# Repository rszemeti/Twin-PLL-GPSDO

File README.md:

# Twin PLL GPSDO

A dual-output GPS-disciplined reference project for Raspberry Pi Pico 2 (RP2350), with:
- Firmware for GPSDO control + PLL programming
- A desktop configuration tool (Windows-friendly)
- A PCB with 2 ADF4351's, GPS module and all the interface bits

## Who this is for
If you need a stable, GPS locked signal source for injection locking 1 or 2 crystal oscillators, or at a push a directly synthesised carrier up to 4.4 GHz.  

It has the advantage over some other units in that the two outputs are truly independently programmable. If you have a microwave transverter for example that needs injection locking and then a 144 to 28MHz converter, you often find that many units only allow the second output to be a fraction of the primary output, which may not produce thw 116 MHz you need. This unit has 2 synthesisers each of which can be programmed as desired.

## Features
- **Output 1 / Output 2 PLL**  Truly indpendent of each other
- **10MHz Auxilliary Output**  For driving other items, eg main radio.
- **Persistent settings** (ADF register writes are auto-committed to EEPROM)
- **Live status LEDs** (GPS fix/lock, satellites, DOP, alarm, lock states)
- **Windows configuration tool** with Main/Details/Tuning/About tabs

## RF output notes
- **Two outputs are fully independent**: each PLL output has its own register set and can be tuned separately.
- **Frequency range**: any frequency within the ADF4351 synthesizer output range is supported in software (approximately **34.375 MHz to 4.4 GHz**).
	- Practical usable range depends on your board layout, output network, filtering, and measurement method.
- **Resolution / step size**:
	- In **Integer-N**, tuning is quantized by $f_{PFD}/\text{OUTDIV}$.
	- With default settings (10 MHz ref, R=5, so $f_{PFD}=2$ MHz), Integer-N step is $2\text{ MHz}/\text{OUTDIV}$ (for example, 62.5 kHz at OUTDIV=32).
	- In **Fractional-N**, finer step sizes are possible (GUI default channel spacing is 1 Hz), but with fractional spurs/tradeoffs.
- **Phase-noise tradeoff**:
	- **Integer-N** is generally preferred for best close-in noise / cleaner spectrum when an exact frequency is possible.
	- **Fractional-N** gives finer frequency placement when exact Integer-N is not available, but may increase spur content.
- **Intended use guidance**:
	- Phase noise is typically **good enough for injection-locking crystal multipliers**.
	- It may **not** be good enough for all **direct multiplication** chains, depending on your multiplier stages and phase-noise budget.

## Repository layout
- `firmware/` – PlatformIO project for Pico 2
- `monitor/` – Python GUI configuration tool app
- `.github/workflows/` – release build automation
- `REFERENCE_LOCKING_README.md` – technical notes on GPS reference locking, PIO timing, interrupts, and timing/error budget

## Quick start (recommended)
### 1) Download a Release
From GitHub Releases, download:
- `Twin-PLL-GPSDO-<tag>.uf2` (firmware)
- `TwinPLLGPSDOMonitor-<tag>.exe` (Windows configuration tool)

### 2) Flash firmware (`.uf2`)
1. Put Pico 2 into BOOTSEL mode.
2. Copy the `.uf2` file to the mounted RP drive.
3. Board reboots automatically.

### 3) Run the configuration tool (`.exe`)
1. Start `TwinPLLGPSDOMonitor-<tag>.exe`.
2. Select COM port and click **Connect**.
3. Use **Set O/P 1** / **Set O/P 2** to configure outputs.

---

## Build from source
## Firmware
Prerequisites:
- Python 3.11+
- PlatformIO

Commands:
```bash
cd firmware
python -m platformio run
```
Upload (example COM port):
```bash
python -m platformio run -t upload --upload-port COM7
```

## Configuration tool (Python)
Prerequisites:
- Python 3.11+

Commands:
```bash
cd monitor
python -m venv .venv
.venv\Scripts\activate
pip install -r requirements.txt
python gpsdo_monitor.py
```

## Configuration tool usage notes
- **Main tab**: front-panel style status + output frequencies + output set buttons
- **Details tab**: logs, decoded registers, DAC/state details
- **About tab**: project links and author links

The configuration tool supports JSON command send for advanced/manual control.

## Persistence behavior
When a PLL/program command is applied:
- Registers are staged
- EEPROM auto-commit is performed in firmware
- On success, firmware emits a success event and the configuration tool shows **Device Updated**

## Releases and updates
On published release, GitHub Actions builds and attaches:
- Firmware UF2
- Configuration tool one-file EXE

So most users can update without local toolchains.

## Troubleshooting
- **Configuration tool cannot connect**: verify correct COM port and close other serial tools.
- **No lock / unstable GPS**: verify antenna visibility and allow warm-up time.
- **Upload issues on Windows**: retry BOOTSEL entry and ensure USB cable supports data.

## Author / links
- Robin Szemeti, G1YFG
- QRZ: https://www.qrz.com/db/G1YFG
- Blog: https://g1yfg.blogspot.com/
- Project repo: https://github.com/rszemeti/Twin-PLL-GPSDO

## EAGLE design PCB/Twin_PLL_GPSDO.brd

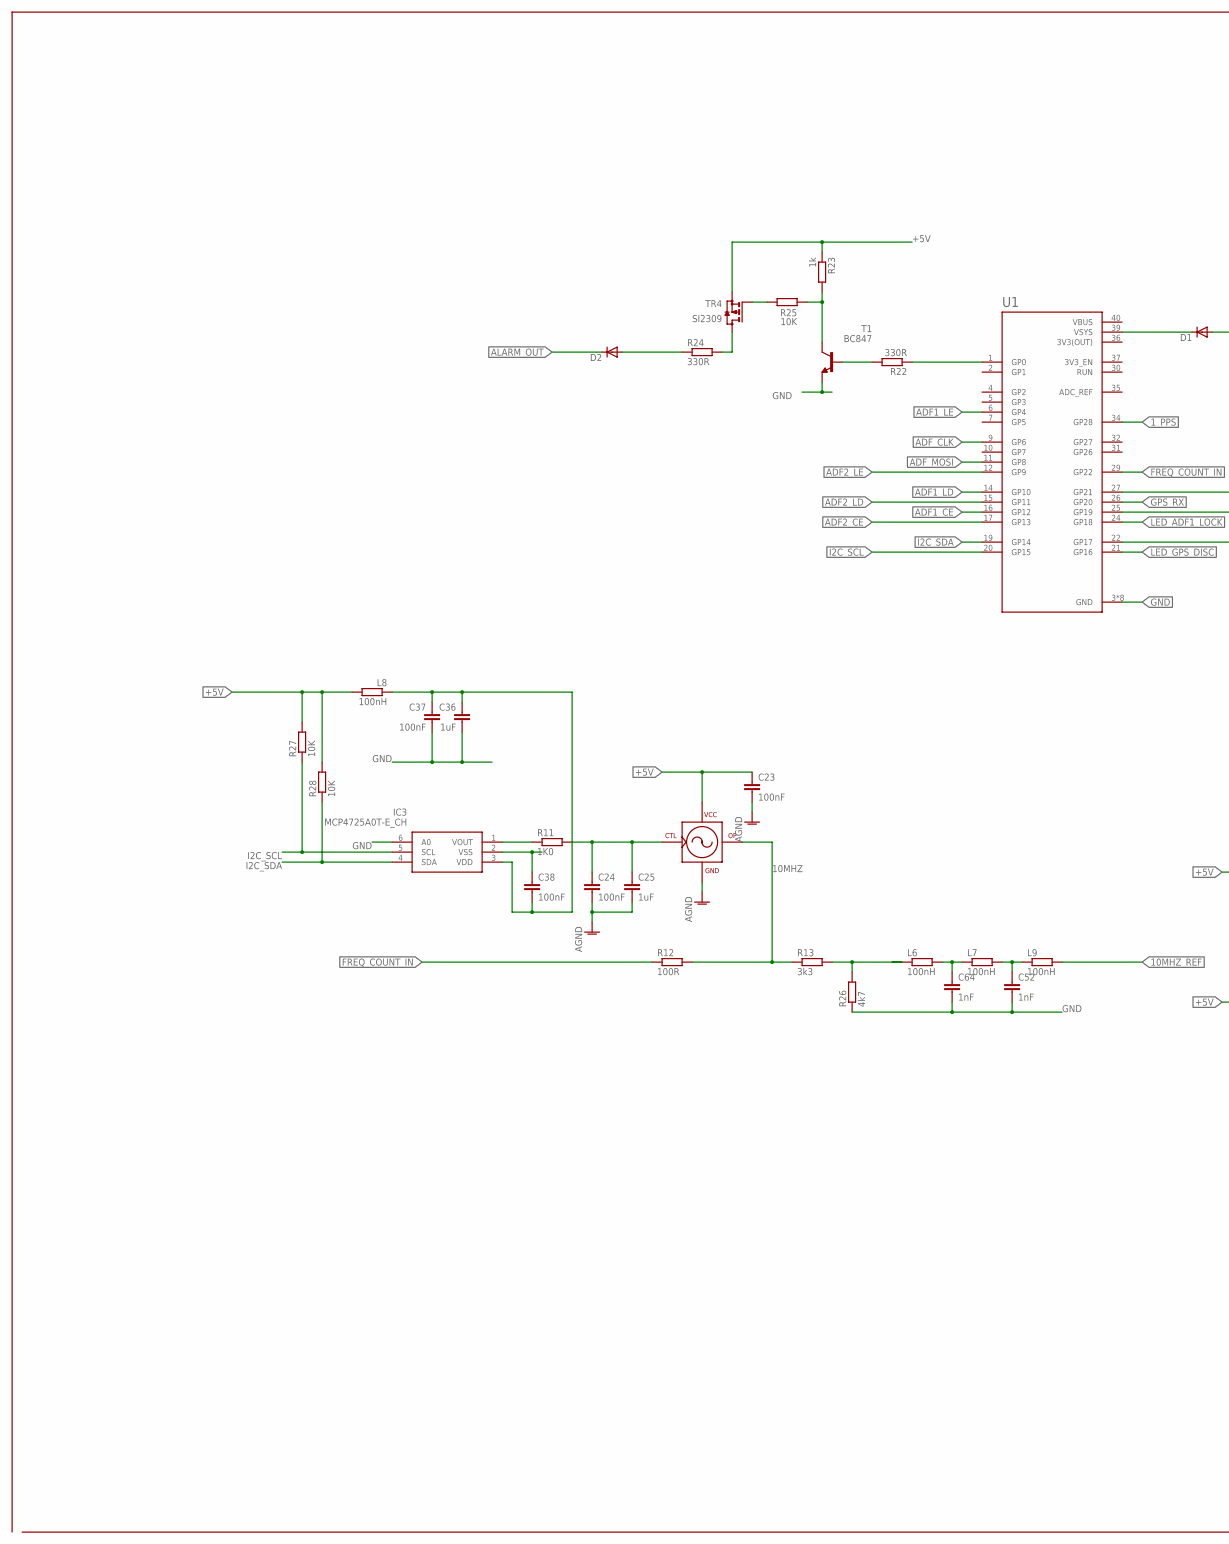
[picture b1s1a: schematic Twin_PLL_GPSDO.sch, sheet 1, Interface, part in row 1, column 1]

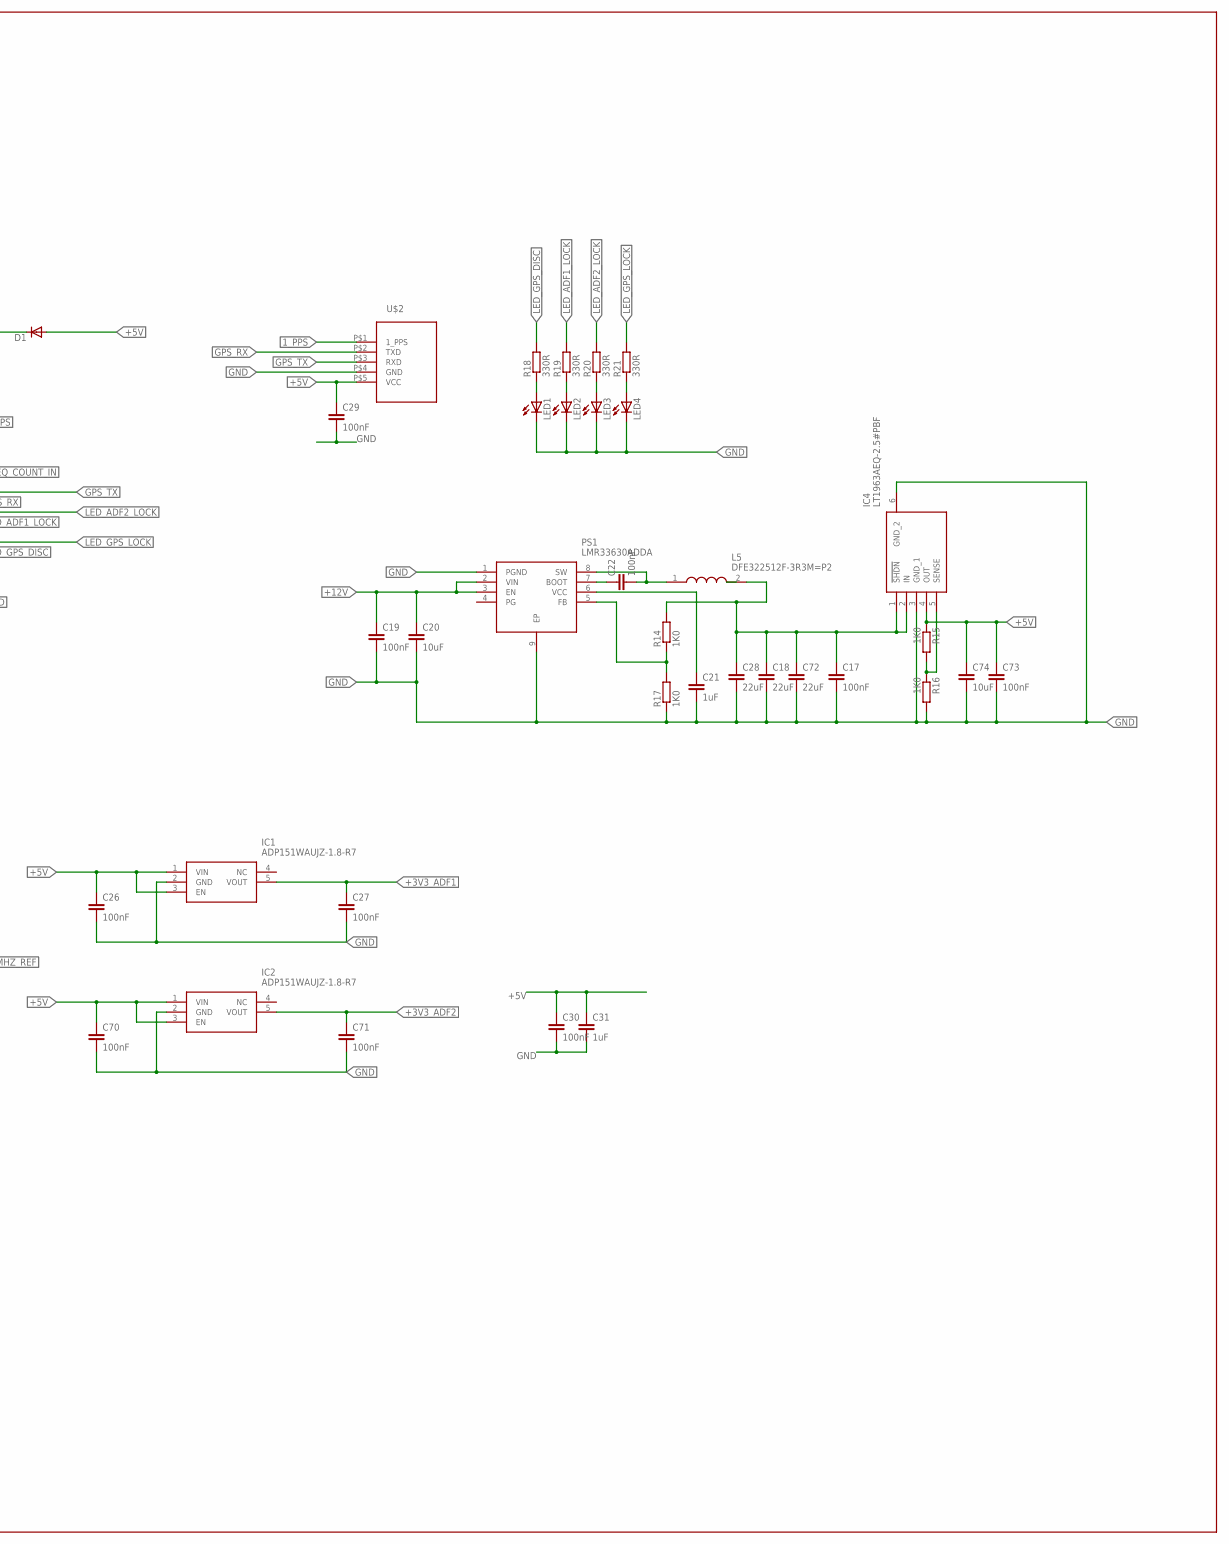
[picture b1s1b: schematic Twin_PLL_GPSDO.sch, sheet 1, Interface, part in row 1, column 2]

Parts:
C17, C19, C22, C26, C27, C29, C70, C71, C73: 100nF; C0805
C18, C28, C72: 22uF; C1210
C20, C74: 10uF; C0805
C21: 1uF; C0805
C23, C24, C30, C37, C38: 100nF; C0603
C25, C31, C36: 1uF; C0603
C52, C64: 1nF; C0603
D1, D2: DIODE-SOD123; SOD123
IC1, IC2: ADP151WAUJZ-1.8-R7; SOT95P280X100-5N
IC3: MCP4725A0T-E_CH; SOT95P270X145-6N
IC4: LT1963AEQ-2.5#PBF; LT1963AEQ25PBF
L5: DFE322512F-3R3M=P2; 1277ASH100MP2; FARNELL_OC 2871467
L6, L7, L8, L9: 100nH; R0603
LED1, LED2, LED3, LED4: LEDCHIPLED_0603; CHIPLED_0603
OSC1: CTI_OSC
PS1: LMR33630ADDA; SOIC127P600X170-9N
R11, R14, R15, R16, R17: 1K0; R0805
R12: 100R; R0805
R13: 3k3; R0603
R18, R19, R20, R21, R22: 330R; R0603
R23: 1k; R0603
R24: 330R; R0805
R25: 10K; R0805
R26: 4k7; R0603
R27, R28: 10K; R0603
T1: BC847; SOT23
TR4: SI2309; SOT23
U1: RASPBERRY_PICO-NO_DEBUGTH; PICO-PKG-TH-STD
U$2: GPS

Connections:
1_PPS: U1.34 (GP28), U$2.P$1 (1_PPS)
3V3(OUT): U1.36 (3V3(OUT))
10MHZ: OSC1.OUT (OP), R12.2, R13.1
10MHZ_REF: L9.2; also elsewhere on the board
+3V3_ADF1: C27.1, IC1.5 (VOUT); also elsewhere on the board
+3V3_ADF2: C71.1, IC2.5 (VOUT); also elsewhere on the board
+5V: C23.1, C26.1, C29.1, C30.1, C31.1, C70.1, C73.1, C74.1, D1.A, IC1.1 (VIN), IC1.3 (EN), IC2.1 (VIN), IC2.3 (EN), IC4.4 (OUT), L8.2, OSC1.VCC, R15.1, R23.1, R27.2, R28.2, TR4.2 (S), U$2.P$5 (VCC)
+12V: C19.1, C20.1, PS1.2 (VIN), PS1.3 (EN)
ADF1_CE: U1.16 (GP12); also elsewhere on the board
ADF1_LD: U1.14 (GP10); also elsewhere on the board
ADF1_LE: U1.6 (GP4); also elsewhere on the board
ADF2_CE: U1.17 (GP13); also elsewhere on the board
ADF2_LD: U1.15 (GP11); also elsewhere on the board
ADF2_LE: U1.12 (GP9); also elsewhere on the board
ADF_CLK: U1.9 (GP6); also elsewhere on the board
ADF_MOSI: U1.11 (GP8); also elsewhere on the board
ALARM_OUT: D2.C
ALARM_PIN: R22.1, U1.1 (GP0)
AVDD: C36.1, C37.1, C38.2, IC3.3 (VDD), L8.1
FREQ_COUNT_IN: R12.1, U1.29 (GP22)
GND: C17.2, C18.2, C19.2, C20.2, C21.2, C23.2, C24.2, C25.2, C26.2, C27.2, C28.2, C29.2, C30.2, C31.2, C36.2, C37.2, C38.1, C52.2, C64.2, C70.2, C71.2, C72.2, C73.2, C74.2, IC1.2 (GND), IC2.2 (GND), IC3.2 (VSS), IC3.6 (A0), IC4.3 (GND_1), IC4.6 (GND_2), LED1.C, LED2.C, LED3.C, LED4.C, OSC1.GND, PS1.1 (PGND), PS1.9 (EP), R16.2, R17.1, R26.1, T1.2 (E), U1.3 (GND), U1.8 (GND), U1.13 (GND), U1.18 (GND), U1.23 (GND), U1.28 (GND), U1.33 (GND), U1.38 (GND), U$2.P$4 (GND); also elsewhere on the board
GPS_RX: U1.26 (GP20), U$2.P$2 (TXD)
GPS_TX: U1.27 (GP21), U$2.P$3 (RXD)
I2C_SCL: IC3.5 (SCL), R27.1, U1.20 (GP15)
I2C_SDA: IC3.4 (SDA), R28.1, U1.19 (GP14)
LED_ADF1_LOCK: R19.2, U1.24 (GP18)
LED_ADF2_LOCK: R20.2, U1.25 (GP19)
LED_GPS_DISC: R18.2, U1.21 (GP16)
LED_GPS_LOCK: R21.2, U1.22 (GP17)
unnamed: IC3.1 (VOUT), R11.1
unnamed: R23.2, R25.2, T1.3 (C)
unnamed: L6.1, R13.2, R26.2
unnamed: LED1.A, R18.1
unnamed: R22.2, T1.1 (B)
unnamed: IC4.5 (SENSE), R15.2, R16.1
unnamed: PS1.5 (FB), R14.1, R17.2
unnamed: C24.1, C25.1, OSC1.REF (CTRL), R11.2
unnamed: C21.1, PS1.6 (VCC)
unnamed: C22.1, PS1.7 (BOOT)
unnamed: C22.2, L5.1, PS1.8 (SW)
unnamed: C17.1, C18.1, C28.1, C72.1, IC4.1 (!SHDN), IC4.2 (IN), L5.2, R14.2
unnamed: LED2.A, R19.1
unnamed: LED3.A, R20.1
unnamed: LED4.A, R21.1
unnamed: D1.C, U1.39 (VSYS)
unnamed: C64.1, L6.2, L7.1
unnamed: R25.1, TR4.1 (G)
unnamed: C52.1, L7.2, L9.1
unnamed: D2.A, R24.1
SWITCH: R24.2, TR4.3 (D)
VBUS: U1.40 (VBUS)

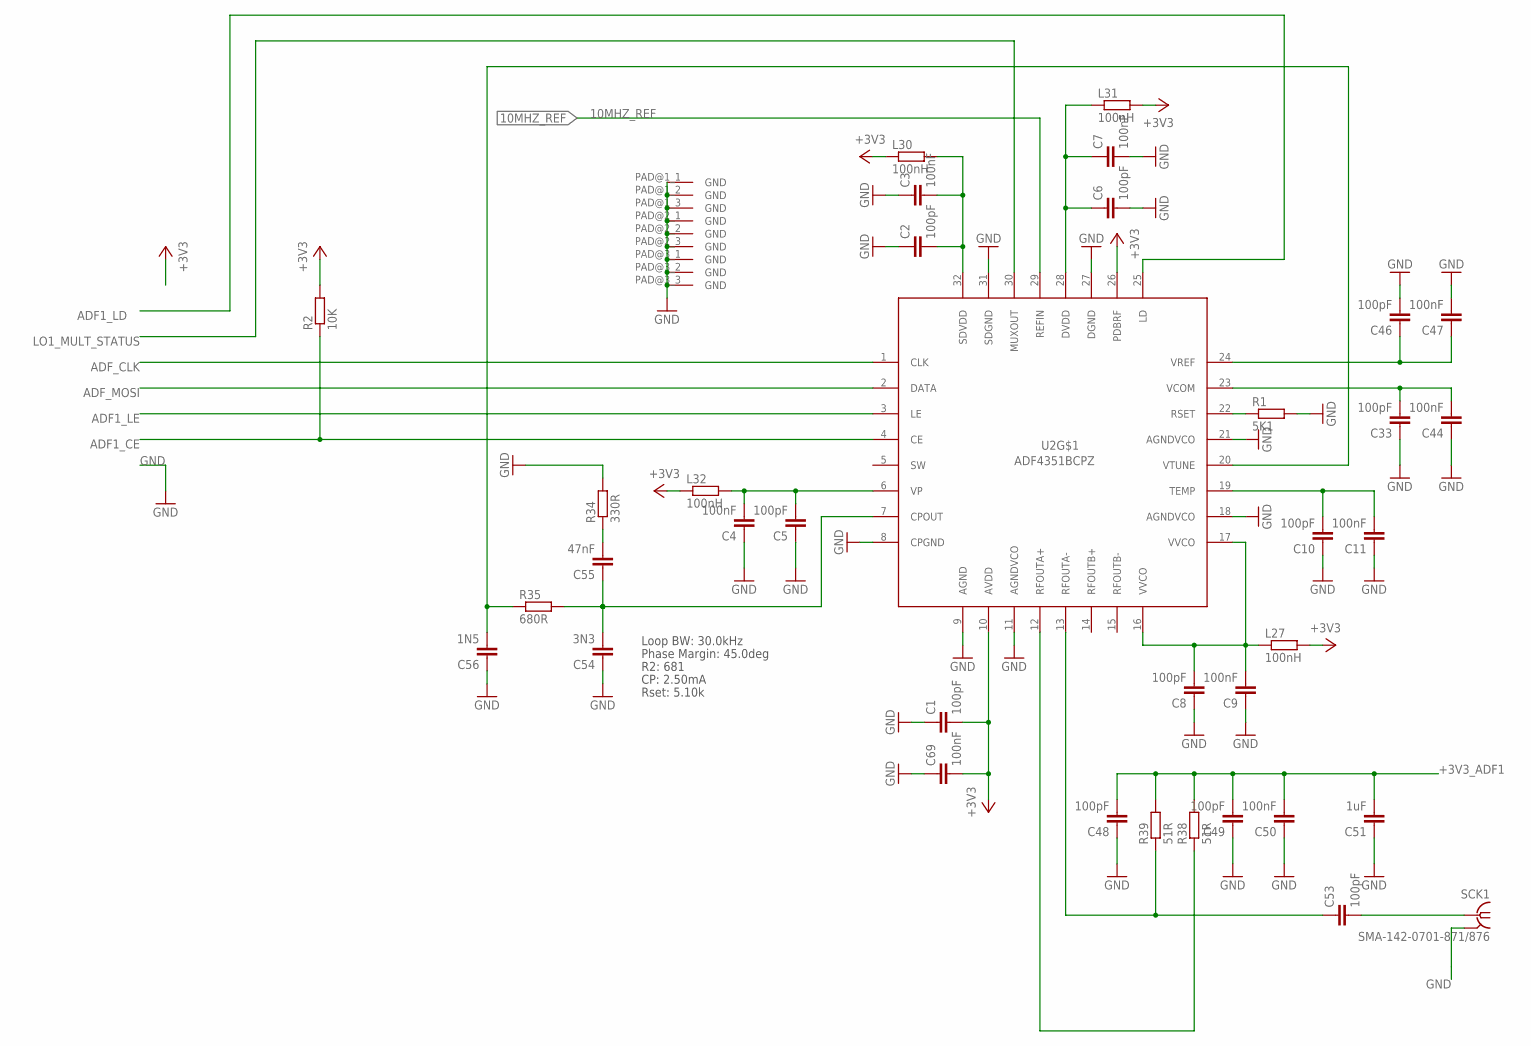
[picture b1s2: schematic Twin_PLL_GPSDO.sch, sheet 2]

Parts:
C1, C2, C5, C6, C8, C10, C33, C46, C48, C49, C53: 100pF; C0603
C3, C4, C7, C9, C11, C44, C47, C50, C69: 100nF; C0603
C51: 1uF; C0603
C54: 3N3; C0603
C55: 47nF; C0603
C56: 1N5; C0603
L27, L30, L31, L32: 100nH; R0603
R1: 5K1; R0603
R2: 10K; R0603
R34: 330R; R0603
R35: 680R; R0603
R38, R39: 51R; R0603
SCK1: SMA-142-0701-871/876; J502-ND-142-0701-871/876; MPN 142-0701-871
U2: ADF4351BCPZ; QFN50P500X500X100-33V2N

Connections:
10MHZ_REF: U2.29 (REFIN); also elsewhere on the board
+3V3_ADF1: C1.2, C48.2, C49.2, C50.2, C51.2, C69.2, L27.2, L30.1, L31.2, L32.1, R2.2, R38.2, R39.2, U2.10 (AVDD), U2.26 (PDBRF); also elsewhere on the board
ADF1_CE: R2.1, U2.4 (CE); also elsewhere on the board
ADF1_LD: U2.25 (LD); also elsewhere on the board
ADF1_LE: U2.3 (LE); also elsewhere on the board
ADF_CLK: U2.1 (CLK); also elsewhere on the board
ADF_MOSI: U2.2 (DATA); also elsewhere on the board
GND: C1.1, C2.1, C3.1, C4.1, C5.1, C6.2, C7.2, C8.1, C9.1, C10.1, C11.1, C33.1, C44.1, C46.2, C47.2, C48.1, C49.1, C50.1, C51.1, C54.1, C56.1, C69.1, R1.2, R34.2, SCK1.G@1 (GND), SCK1.G@2 (GND), SCK1.G@3 (GND), SCK1.G@4 (GND), U2.8 (CPGND), U2.9 (AGND), U2.11 (AGNDVCO), U2.18 (AGNDVCO), U2.21 (AGNDVCO), U2.27 (DGND), U2.31 (SDGND), U2.PAD@1_1 (GND), U2.PAD@1_2 (GND), U2.PAD@1_3 (GND), U2.PAD@2_1 (GND), U2.PAD@2_2 (GND), U2.PAD@2_3 (GND), U2.PAD@3_1 (GND), U2.PAD@3_2 (GND), U2.PAD@3_3 (GND); also elsewhere on the board
LO1_MULT_STATUS: U2.30 (MUXOUT)
unnamed: C10.2, C11.2, U2.19 (TEMP)
unnamed: C33.2, C44.2, U2.23 (VCOM)
unnamed: C46.1, C47.1, U2.24 (VREF)
unnamed: C4.2, C5.2, L32.2, U2.6 (VP)
unnamed: C2.2, C3.2, L30.2, U2.32 (SDVDD)
unnamed: R1.1, U2.22 (RSET)
unnamed: R38.1, U2.12 (RFOUTA+)
unnamed: C53.1, R39.1, U2.13 (RFOUTA-)
unnamed: C54.2, C55.1, R35.2, U2.7 (CPOUT)
unnamed: C56.2, R35.1, U2.20 (VTUNE)
unnamed: C55.2, R34.1
unnamed: C6.1, C7.1, L31.1, U2.28 (DVDD)
unnamed: C8.2, C9.2, L27.1, U2.16 (VVCO), U2.17 (VVCO)
unnamed: C53.2, SCK1.1

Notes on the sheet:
Loop BW: 30.0kHz
Phase Margin: 45.0deg
R2: 681
CP: 2.50mA
Rset: 5.10k

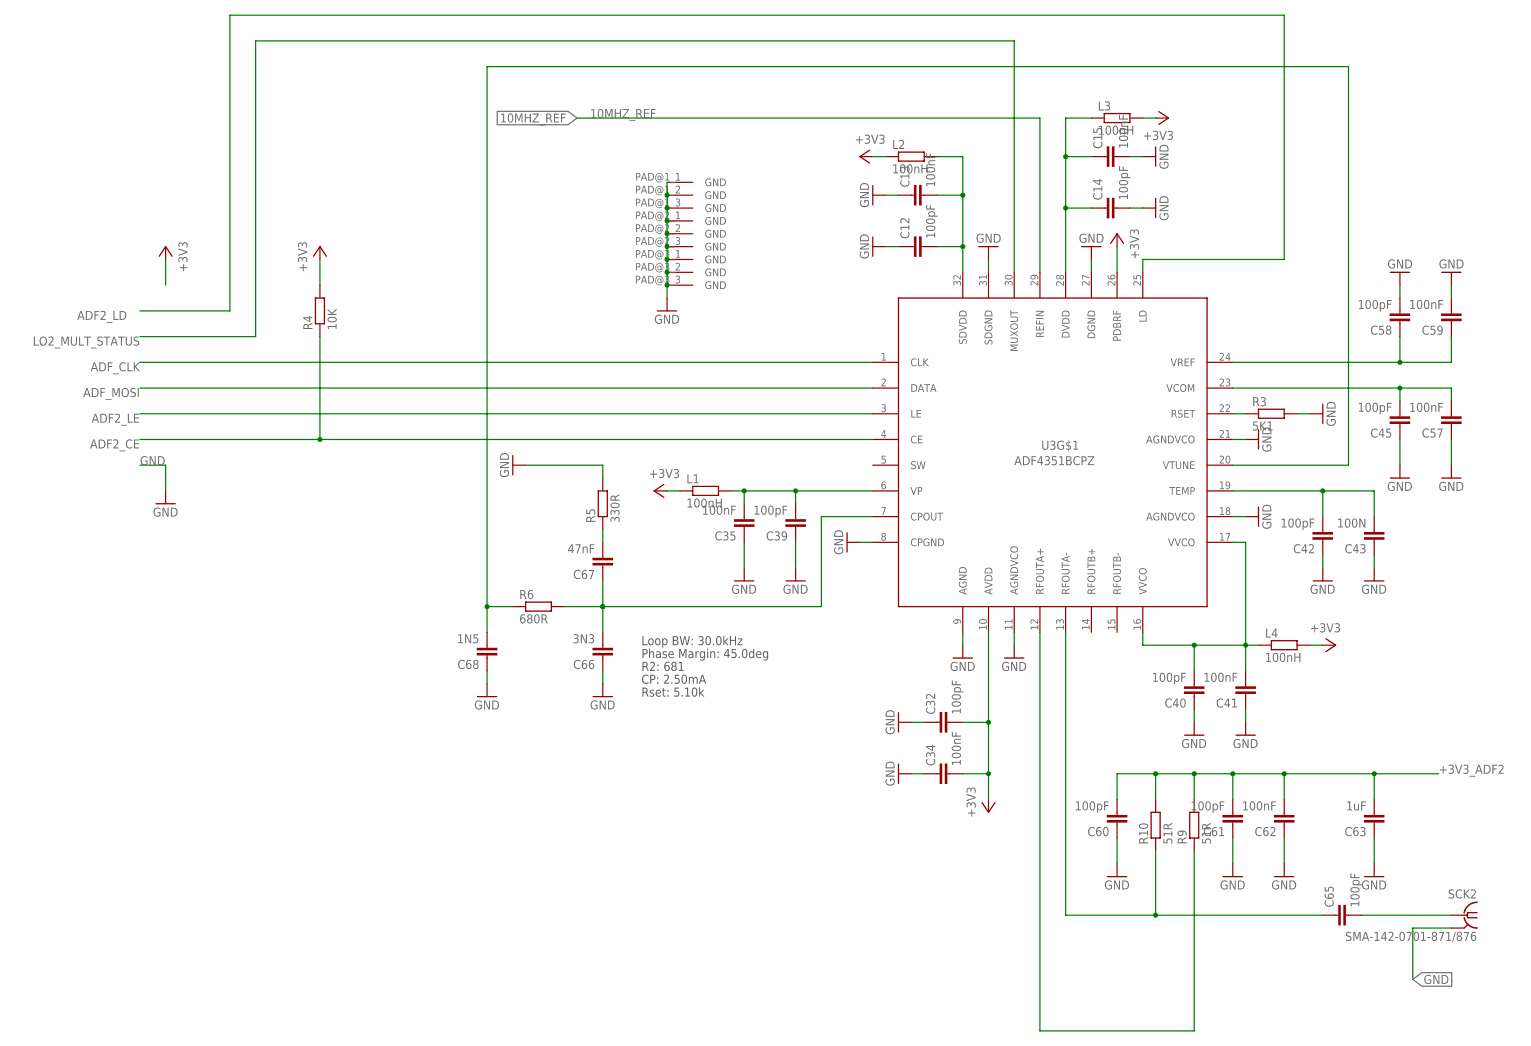
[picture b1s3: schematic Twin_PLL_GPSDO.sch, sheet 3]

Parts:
C12, C14, C32, C39, C40, C42, C45, C58, C60, C61, C65: 100pF; C0603
C13, C15, C34, C35, C41, C57, C59, C62: 100nF; C0603
C43: 100N; C0603
C63: 1uF; C0603
C66: 3N3; C0603
C67: 47nF; C0603
C68: 1N5; C0603
L1, L2, L3, L4: 100nH; R0603
R3: 5K1; R0603
R4: 10K; R0603
R5: 330R; R0603
R6: 680R; R0603
R9, R10: 51R; R0603
SCK2: SMA-142-0701-871/876; J502-ND-142-0701-871/876; MPN 142-0701-871
U3: ADF4351BCPZ; QFN50P500X500X100-33V2N

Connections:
10MHZ_REF: U3.29 (REFIN); also elsewhere on the board
+3V3_ADF2: C32.2, C34.2, C60.2, C61.2, C62.2, C63.2, L1.1, L2.1, L3.2, L4.2, R4.2, R9.2, R10.2, U3.10 (AVDD), U3.26 (PDBRF); also elsewhere on the board
ADF2_CE: R4.1, U3.4 (CE); also elsewhere on the board
ADF2_LD: U3.25 (LD); also elsewhere on the board
ADF2_LE: U3.3 (LE); also elsewhere on the board
ADF_CLK: U3.1 (CLK); also elsewhere on the board
ADF_MOSI: U3.2 (DATA); also elsewhere on the board
GND: C12.1, C13.1, C14.2, C15.2, C32.1, C34.1, C35.1, C39.1, C40.1, C41.1, C42.1, C43.1, C45.1, C57.1, C58.2, C59.2, C60.1, C61.1, C62.1, C63.1, C66.1, C68.1, R3.2, R5.2, SCK2.G@1 (GND), SCK2.G@2 (GND), SCK2.G@3 (GND), SCK2.G@4 (GND), U3.8 (CPGND), U3.9 (AGND), U3.11 (AGNDVCO), U3.18 (AGNDVCO), U3.21 (AGNDVCO), U3.27 (DGND), U3.31 (SDGND), U3.PAD@1_1 (GND), U3.PAD@1_2 (GND), U3.PAD@1_3 (GND), U3.PAD@2_1 (GND), U3.PAD@2_2 (GND), U3.PAD@2_3 (GND), U3.PAD@3_1 (GND), U3.PAD@3_2 (GND), U3.PAD@3_3 (GND); also elsewhere on the board
LO2_MULT_STATUS: U3.30 (MUXOUT)
unnamed: C42.2, C43.2, U3.19 (TEMP)
unnamed: C45.2, C57.2, U3.23 (VCOM)
unnamed: C58.1, C59.1, U3.24 (VREF)
unnamed: R3.1, U3.22 (RSET)
unnamed: R9.1, U3.12 (RFOUTA+)
unnamed: C65.1, R10.1, U3.13 (RFOUTA-)
unnamed: C66.2, C67.1, R6.2, U3.7 (CPOUT)
unnamed: C68.2, R6.1, U3.20 (VTUNE)
unnamed: C67.2, R5.1
unnamed: C35.2, C39.2, L1.2, U3.6 (VP)
unnamed: C12.2, C13.2, L2.2, U3.32 (SDVDD)
unnamed: C14.1, C15.1, L3.1, U3.28 (DVDD)
unnamed: C40.2, C41.2, L4.1, U3.16 (VVCO), U3.17 (VVCO)
OUTPUT: C65.2, SCK2.1

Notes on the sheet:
Loop BW: 30.0kHz
Phase Margin: 45.0deg
R2: 681
CP: 2.50mA
Rset: 5.10k

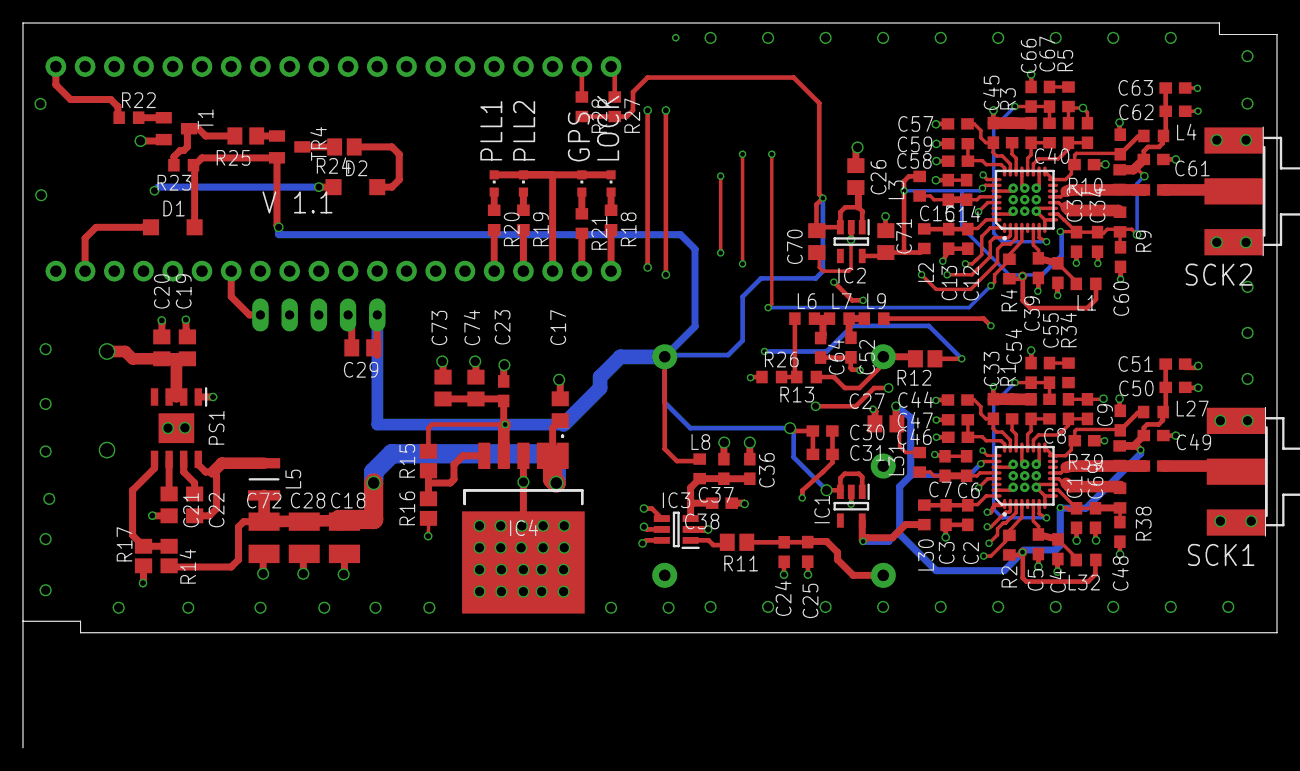
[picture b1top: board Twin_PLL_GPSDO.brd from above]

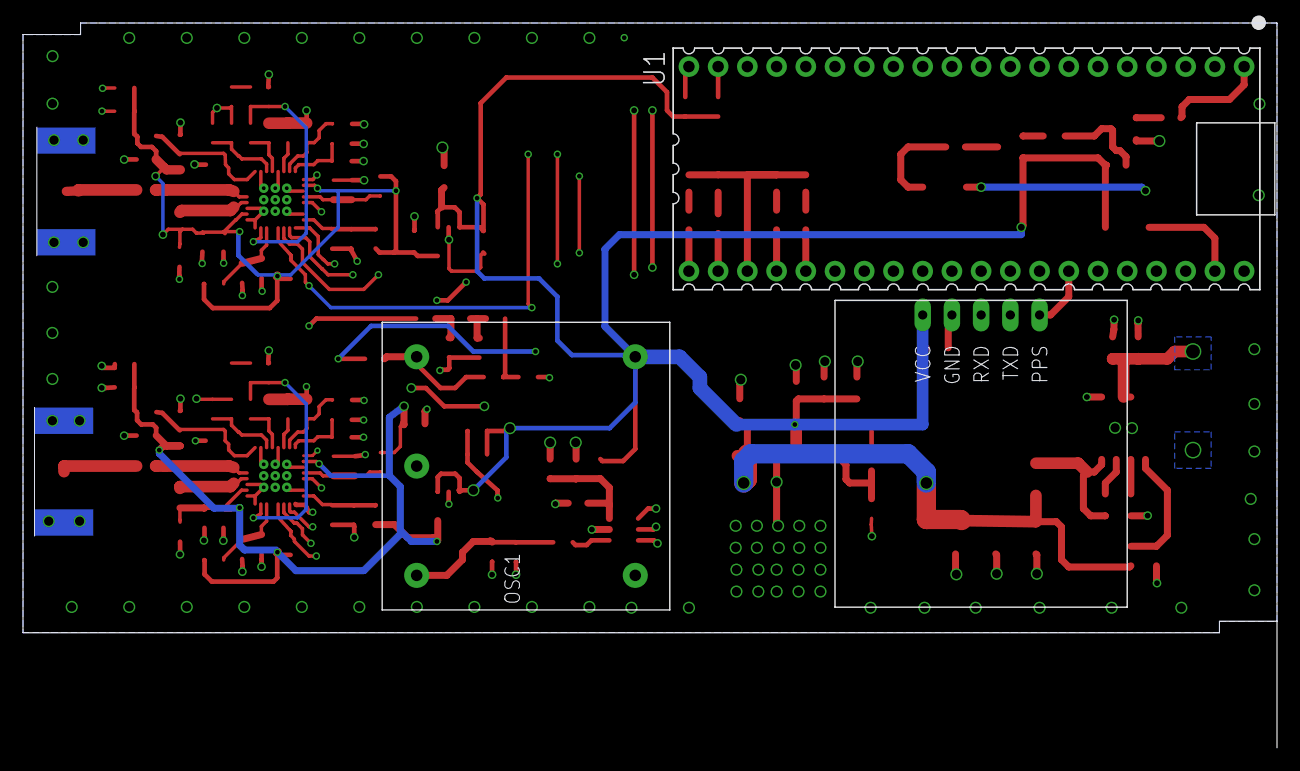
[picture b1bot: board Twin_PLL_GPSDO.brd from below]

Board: 4 copper layers, 109.0 x 63.0 mm, 136 parts (3 on the bottom side), 76 nets.

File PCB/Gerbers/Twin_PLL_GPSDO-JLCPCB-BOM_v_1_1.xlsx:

Comment | Designator | Footprint | JLCPCB Part #（optional）
100pF | C1, C2, C5, C6, C8, C10, C12, C14, C32, C33, C39, C40, C42, C45, C46, C48, C49,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 | C0603
22uF | C18, C28, C72 | C1210
10uF | C20, C74 | C0805
1uF | C21 | C0805
100nF | C3, C4, C7, C9, C11, C13, C15, C23, C24, C30, C34, C35, C37, C38, C41, C43, C44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 | C0603
100nF | C17, C19, C22, C26, C27, C29, C70, C71, C73 | C0805
1uF | C25, C31, C36, C51, C63 | C0603
1nF | C52, C64 | C0603
3.3nF | C54, C66 | C0603
47nF | C55, C67 | C0603
1.5nF | C56, C68 | C0603
ADP151WAUJZ-1.8-R7 | IC1, IC2 | SOT95P280X100-5N
MCP4725A0T-E_CH | IC3 | SOT95P270X145-6N
LT1963AEQ-2.5#PBF | IC4 | LT1963AEQ25PBF
DFE322512F-3R3M=P2 | L5 | 1277ASH100MP2
100nH | L1, L2, L3, L4, L6, L7, L8, L9, L27, L30, L31, L32 | R0603
 | LED1, LED2, LED3, LED4 | CHIPLED_0603
CTI_OSC | OSC1 | CTI_OSC
LMR33630ADDA | PS1 | SOIC127P600X170-9N
5.1K | R1, R3 | R0603
10K | R2, R4 | R0603
1K | R11, R14, R15, R16, R17 | R0805
100R | R12 | R0805
3.3K | R13 | R0603
1K | R23 | R0603
330R | R24 | R0805
10K | R25 | R0805
4.7K | R26 | R0603
330R | R5, R18, R19, R20, R21, R22, R34 | R0603
680R | R6, R35 | R0603
0R | R7, R36 | R0603
NF | R8, R37 | R0603
51R | R9, R10, R38, R39 | R0603
SMA-142-0701-871/876 | SCK1, SCK2 | J502-ND-142-0701-871/876
BC847 | T1 | SOT23
SI2309 | TR4 | SOT23
 | U1 | PICO-PKG-TH-STD
ADF4351BCPZ | U2, U3 | QFN50P500X500X100-33V2N
GPS | U$2 | GPS

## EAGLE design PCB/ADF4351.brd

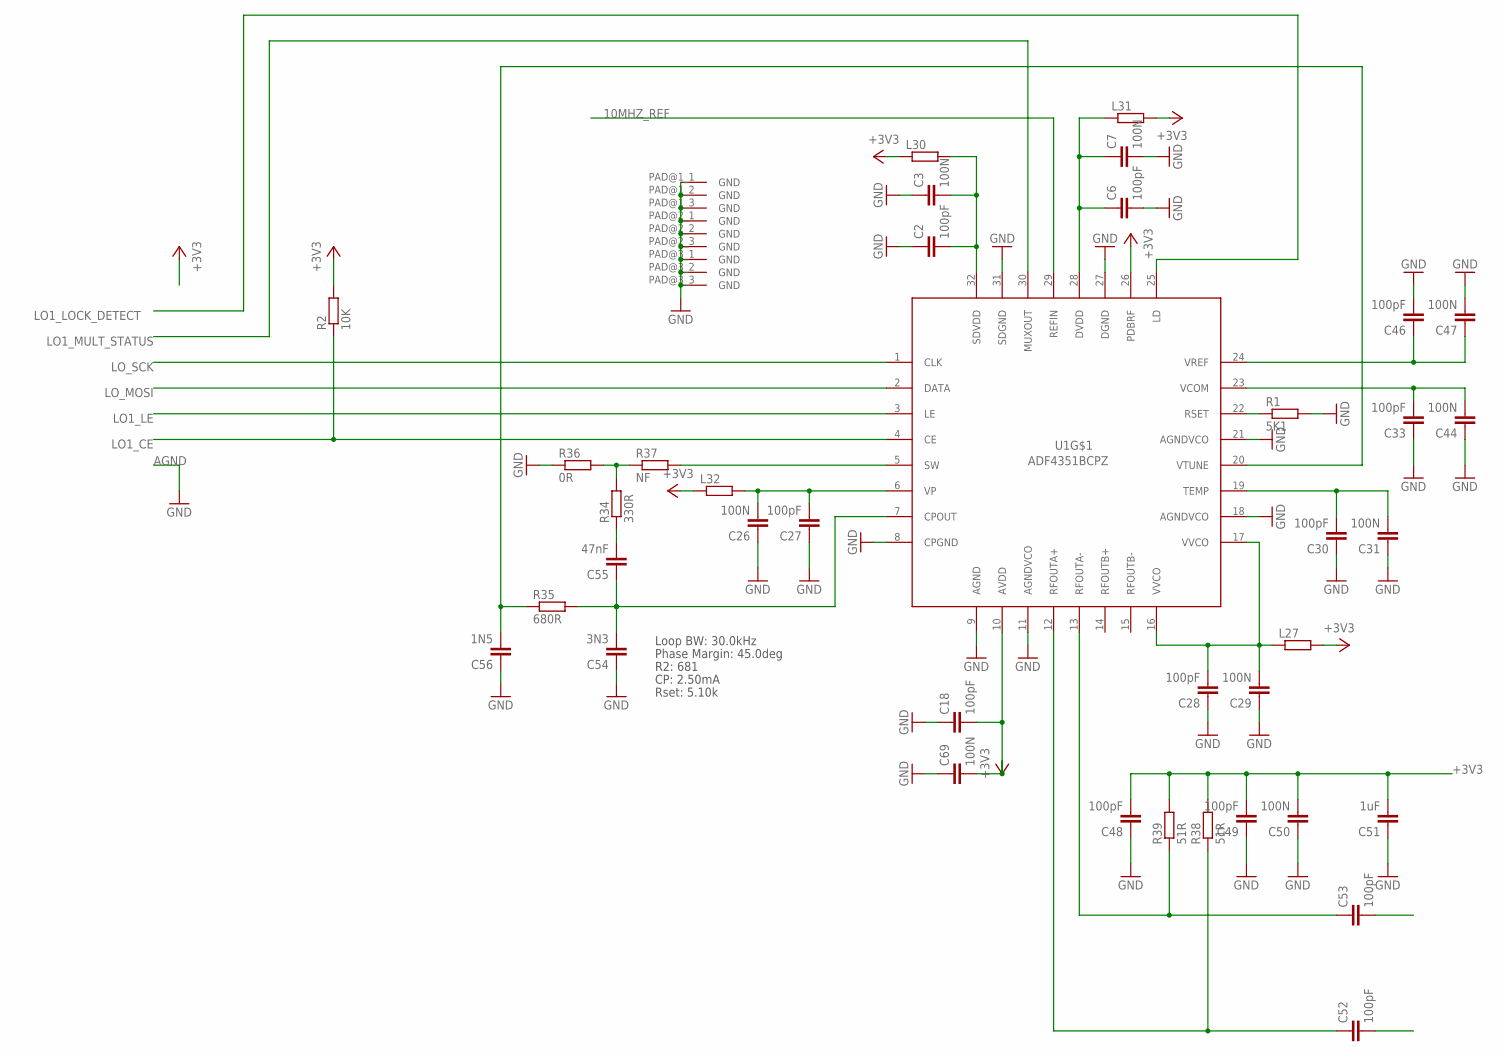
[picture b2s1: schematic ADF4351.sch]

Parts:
C2, C6, C18, C27, C28, C30, C33, C46, C48, C49, C52, C53: 100pF; C0603
C3, C7, C26, C29, C31, C44, C47, C50, C69: 100N; C0603
C51: 1uF; C0603
C54: 3N3; C0603
C55: 47nF; C0603
C56: 1N5; C0603
L27, L30, L31, L32: R-EU_R0603; R0603
R1: 5K1; R0603
R2: 10K; R0603
R34: 330R; R0603
R35: 680R; R0603
R36: 0R; R0603
R37: NF; R0603
R38, R39: 51R; R0603
U1: ADF4351BCPZ; QFN50P500X500X100-33V2N

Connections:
10MHZ_REF: U1.29 (REFIN)
+3V3: C18.2, C48.2, C49.2, C50.2, C51.2, C69.2, L27.2, L30.1, L31.2, L32.1, R2.2, R38.2, R39.2, U1.10 (AVDD), U1.26 (PDBRF)
AGND: C2.1, C3.1, C6.2, C7.2, C18.1, C26.1, C27.1, C28.1, C29.1, C30.1, C31.1, C33.1, C44.1, C46.2, C47.2, C48.1, C49.1, C50.1, C51.1, C54.1, C56.1, C69.1, R1.2, R36.1, U1.8 (CPGND), U1.9 (AGND), U1.11 (AGNDVCO), U1.18 (AGNDVCO), U1.21 (AGNDVCO), U1.27 (DGND), U1.31 (SDGND), U1.PAD@1_1 (GND), U1.PAD@1_2 (GND), U1.PAD@1_3 (GND), U1.PAD@2_1 (GND), U1.PAD@2_2 (GND), U1.PAD@2_3 (GND), U1.PAD@3_1 (GND), U1.PAD@3_2 (GND), U1.PAD@3_3 (GND)
LO1_CE: R2.1, U1.4 (CE)
LO1_LE: U1.3 (LE)
LO1_LOCK_DETECT: U1.25 (LD)
LO1_MULT_STATUS: U1.30 (MUXOUT)
LO_MOSI: U1.2 (DATA)
LO_SCK: U1.1 (CLK)
unnamed: C30.2, C31.2, U1.19 (TEMP)
unnamed: C33.2, C44.2, U1.23 (VCOM)
unnamed: C46.1, C47.1, U1.24 (VREF)
unnamed: C26.2, C27.2, L32.2, U1.6 (VP)
unnamed: C2.2, C3.2, L30.2, U1.32 (SDVDD)
unnamed: R1.1, U1.22 (RSET)
unnamed: C52.1, R38.1, U1.12 (RFOUTA+)
unnamed: C53.1, R39.1, U1.13 (RFOUTA-)
unnamed: C54.2, C55.1, R35.2, U1.7 (CPOUT)
unnamed: C56.2, R35.1, U1.20 (VTUNE)
unnamed: C55.2, R34.1
unnamed: R34.2, R36.2, R37.1
unnamed: R37.2, U1.5 (SW)
unnamed: C6.1, C7.1, L31.1, U1.28 (DVDD)
unnamed: C28.2, C29.2, L27.1, U1.16 (VVCO), U1.17 (VVCO)

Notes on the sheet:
Loop BW: 30.0kHz
Phase Margin: 45.0deg
R2: 681
CP: 2.50mA
Rset: 5.10k

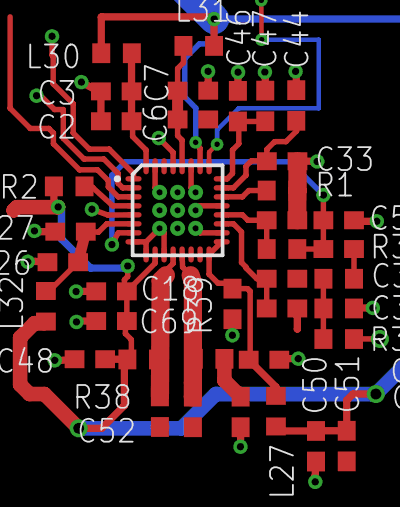
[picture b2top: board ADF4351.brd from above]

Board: 4 copper layers, 38 parts (0 on the bottom side), 18 nets.

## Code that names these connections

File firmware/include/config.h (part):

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
// --- GPS ---
#define GPS_UART        uart1
#define GPS_TX_PIN      20   // Pico TX → GPS module RX  (schematic: GPS_RX)
#define GPS_RX_PIN      21   // Pico RX ← GPS module TX  (schematic: GPS_TX)
#define GPS_1PPS_PIN    28
#define GPS_BAUD        9600

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// so these pins are clocked manually in adf4351.cpp rather than via the
// Arduino SPI peripheral. Fixed by hardware wiring, not configurable.
#define ADF_SCK_PIN     6    // shared SCK
#define ADF_MOSI_PIN    8    // shared MOSI / TX

// --- ADF4351 #1 (104 MHz) ---
#define ADF1_LE_PIN     4    // latch enable
#define ADF1_CE_PIN     12
#define ADF1_LD_PIN     10   // lock detect

// Default PLL1 enable state (runtime-configurable via pll_ctrl command).
#define ADF1_ENABLED_DEFAULT  1

// --- ADF4351 #2 (116 MHz) ---
#define ADF2_LE_PIN     9    // latch enable
#define ADF2_CE_PIN     13
#define ADF2_LD_PIN     11   // lock detect

// Default PLL2 enable state (runtime-configurable via pll_ctrl command).
#define ADF2_ENABLED_DEFAULT  1
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// --- I2C for MCP4725 DAC (OCXO EFC) ---
// GPIO14/15 are only valid I2C1 pins (Wire1), not I2C0 (Wire) — code must
// use Wire1.setSDA()/setSCL() to match, not the default Wire instance.
#define I2C_SDA_PIN     14
#define I2C_SCL_PIN     15
#define MCP4725_ADDR    0x60  // A0 tied low

// --- PWM DAC option (bypass MCP4725 for quick bench test) ---
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#define PWM_DAC_PIN     25

// --- Status LEDs ---
#define LED_GPS_DISC    16   // GPS discipline active
#define LED_GPS_LOCK    17   // GPS lock
#define LED_ADF1_LOCK   18
#define LED_ADF2_LOCK   19
#define LED_ALARM       27

// Additional spare LEDs (optional, not on schematic)
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#define LED_SATS_USED   24

// --- Alarm output (open collector via BC847 + R22) ---
#define ALARM_PIN       0

// --- Debug UART ---
#define DEBUG_TX_PIN    3
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
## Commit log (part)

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2026-03-17 Release v0.0.1
2026-03-17 Update release-artifacts.yml
    with latest version pinning
2026-03-17 automated taggng of release build in fw
2026-03-17 auto version pickup
2026-03-17 v0.0.7
    added registers button for direct register entry
    added tech readmo
2026-03-17 First attempt at manual
2026-03-17 manual ... attempt 2
2026-03-17 PID tuning dialogue
2026-03-17 readme improvements
2026-03-17 minor UI tweaks
2026-03-17 PDF build image include problem hopefully fixed
2026-03-27 Add GPSDO debug telemetry and minimal PPS counter tests
2026-03-27 Working 1
    working on bench locking 10MHtcxo to gps
2026-03-27 Lock detection attempt2
    Still trying to get a reliable "I am locked" decision
2026-03-27 update refence locking description
2026-03-27 Revert to Mermaid diagram
2026-03-27 variabel renaming an document
2026-03-27 Lock detect attempt 4?
2026-03-28 Lock detection working!
2026-03-28 EEPROM.begin() before disc.begin(), 30s warmup
2026-03-28 GUI Update, settings update
2026-03-28 Count accumulator loop: integer ring buffer, double integrator, zero-on-lock, count_err_sum in status
2026-03-29 Fix double integration: feed average count error to PI loop, I_GAIN=5.0
    - discipliner.update() now takes double avgCountError instead of int64_t sum
    - main.cpp computes (double)windowSum / usable before calling update()
    - I_GAIN bumped to 5.0 (locked eff=2.5) for ~30s convergence
    - DISC_CTRL_VERSION bumped to 5 to force fresh gains over stale EEPROM
    - Verified: converges to count_err_sum=0, DAC stable at lock point
2026-03-29 Update REFERENCE_LOCKING_README for integer count accumulator architecture
    - Signal flow diagram updated: ring buffer + average count error path
    - Section 3 rewritten: integer ring buffer, running sum, avg/N to integrator
    - Gain units clarified: DAC counts per Hz-error (not ppb-based 1/N scaling)
    - Current defaults: I_GAIN=5.0, locked ratio=0.5, window 16s/64s
    - Telemetry fields updated: disc_count_err, disc_avg_count_err, count_err_sum
    - Quick reference table updated with current values
2026-03-29 Monitor: add count_err_sum and avg count error to tuning Status box
    - Tuning Status box now shows Avg count err (Hz) and Count err sum
    - Overview details label updated: 'Disc avg freq err (ppb)' -> 'Disc avg count err (Hz)'
    - Parse disc_avg_count_err and count_err_sum from renamed JSON fields
    - Reset new labels on disconnect
2026-03-29 Monitor: update disc presets for count-error-in-Hz gain units
    - slow: i_gain 0.10 -> 2.0
    - normal: i_gain 0.20 -> 5.0 (matches config.h default)
    - fast: i_gain 0.40 -> 10.0
2026-03-29 README: clarify ppb is telemetry-only, not in control path
2026-03-29 README: clarify windowed int64_t sum is bounded, not unbounded accumulation
2026-03-29 Update manual screenshots and capture script for count-error control loop
2026-03-29 Fix About screenshot (was showing Save/Restore), add Save/Restore screenshot
2026-03-29 Make PLL1/PLL2 enable runtime-configurable with CE control and alarm exclusion
    - Replace compile-time ADF1_INSTALLED/ADF2_INSTALLED with runtime g_adf1Enabled/g_adf2Enabled
    - Add pll_ctrl JSON command for get/set of PLL enable state
    - Drive CE line low on disabled PLLs via adf.enable(false)
    - Disabled PLLs excluded from alarm logic and lock watchdog
    - Persist PLL enable state in DiscCtrlBlob v6 (EEPROM)
    - Add Enabled checkbox to PLL1/PLL2 boxes in monitor GUI
2026-03-29 Add adf1/2_enabled to saved_disc_ctrl telemetry event
2026-03-29 PCB catchup
2026-03-29 Rename ADF1/ADF2 Lock to PLL1/PLL2 Lock in GUI virtual LEDs

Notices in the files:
parts and their libraries:
Document: This design is licensed under a Creative Commons Attribution-ShareAlike
Document: 3.0 Unported License: http://creativecommons.org/licenses/by-sa/3.0
